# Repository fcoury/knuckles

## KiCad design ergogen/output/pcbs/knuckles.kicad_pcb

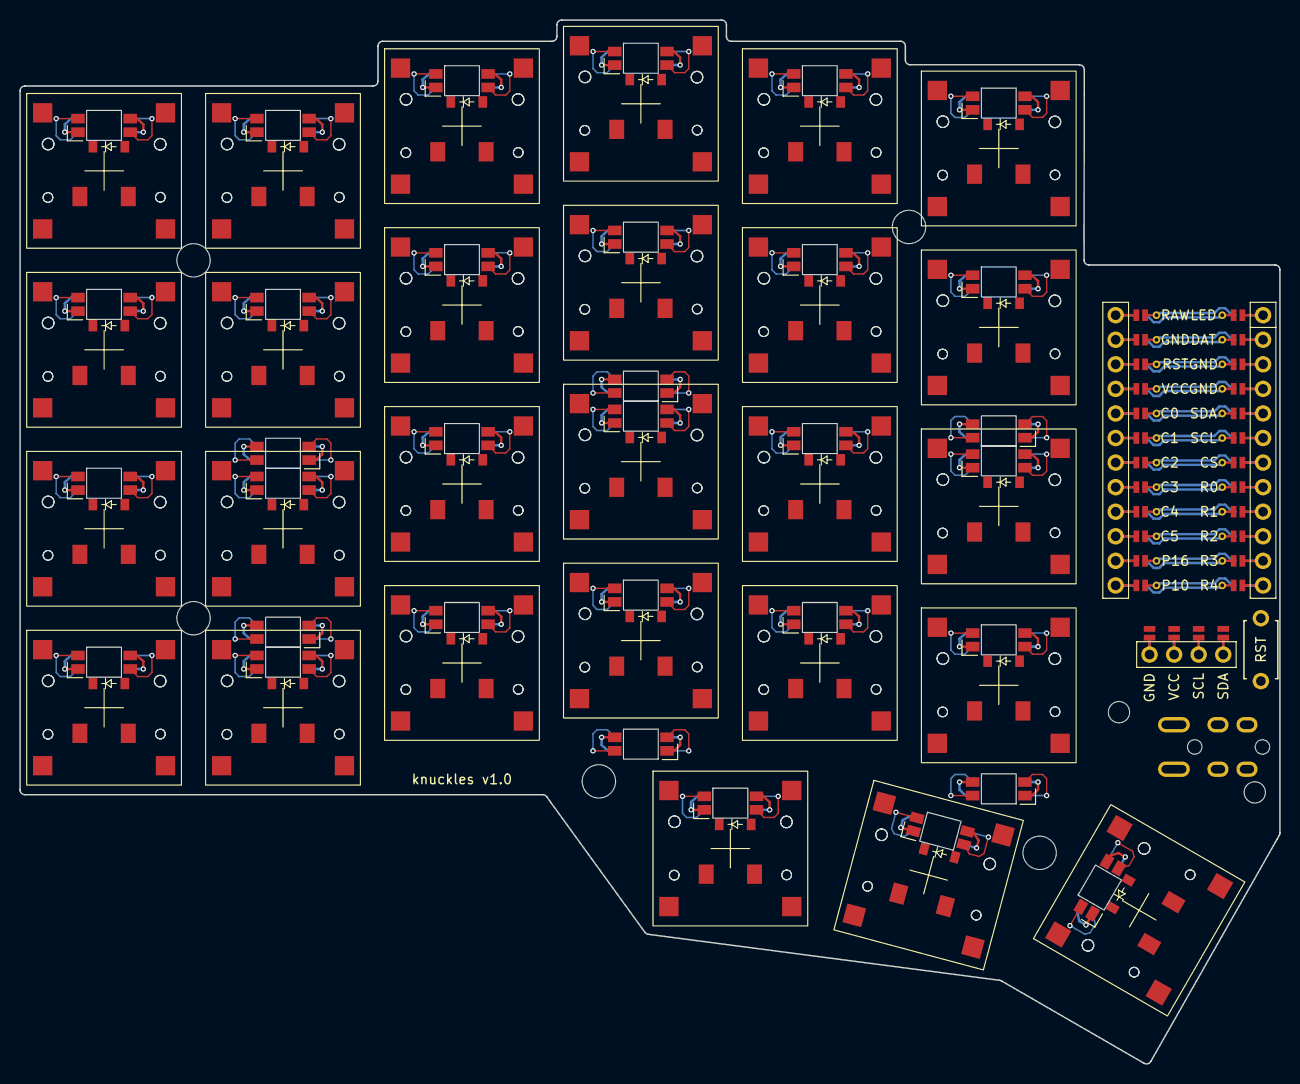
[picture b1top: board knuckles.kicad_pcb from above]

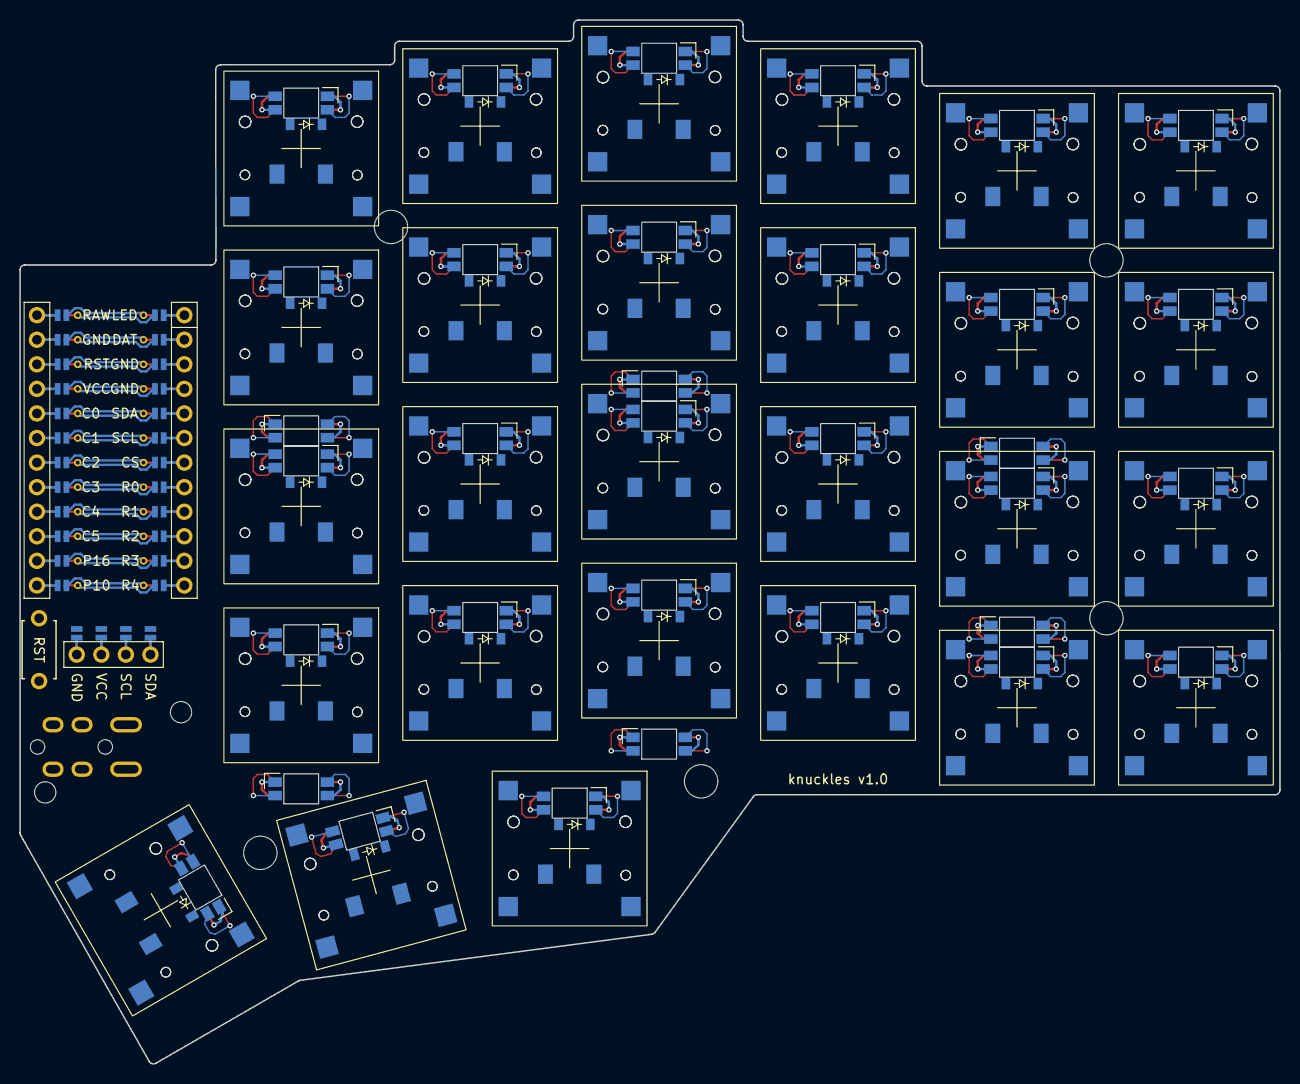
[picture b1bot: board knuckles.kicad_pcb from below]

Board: 2 copper layers, 130.3 x 107.9 mm, 152 parts (87 on the bottom side), 102 nets.

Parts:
D1, D2, D3, D4, D5, D6, D7, D8, D9, D10, D11, D12, D13, D14, D15, D16, D17, D18, D19, D20, D21, D22, D23, D24, D25, D26, D27, D28, D29, D30, D31, D32, D33, D34, D35, D36, D37, D38, D39, D40, D41, D42, D43, D44, D45, D46, D47, D48, D49, D50, D51, D52, D53, D54: diode_tht_sod123
DISP1: display_ssd1306
LED1, LED2, LED3, LED4, LED5, LED6, LED7, LED8, LED9, LED10, LED11, LED12, LED13, LED14, LED15, LED16, LED17, LED18, LED19, LED20, LED21, LED22, LED23, LED24, LED25, LED26, LED27: led_SK6812mini-e (per-key, reversible)
LED28, LED29, LED30, LED31, LED32, LED33: led_SK6812mini-e (underglow, reversible)
MCU1: mcu_nice_nano
MH1, MH2, MH3, MH4, MH5, MH6, MH7: mounting_hole_npth
RST1: reset_switch_tht_top
S1, S2, S3, S4, S5, S6, S7, S8, S9, S10, S11, S12, S13, S14, S15, S16, S17, S18, S19, S20, S21, S22, S23, S24, S25, S26, S27, S28, S29, S30, S31, S32, S33, S34, S35, S36, S37, S38, S39, S40, S41, S42, S43, S44, S45, S46, S47, S48, S49, S50, S51, S52, S53, S54: CPG1316S01D02
TRRS1: trrs_pj320a (reversible, symmetric)

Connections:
C0: MCU1.120, S1.1, S2.1, S3.1, S4.1, S28.1, S29.1, S30.1, S31.1
C1: MCU1.119, S5.1, S6.1, S7.1, S8.1, S32.1, S33.1, S34.1, S35.1
C2: MCU1.118, S9.1, S10.1, S11.1, S12.1, S36.1, S37.1, S38.1, S39.1
C3: MCU1.117, S13.1, S14.1, S15.1, S16.1, S25.1, S40.1, S41.1, S42.1, S43.1, S52.1
C4: MCU1.116, S17.1, S18.1, S19.1, S20.1, S26.1, S44.1, S45.1, S46.1, S47.1, S53.1
C5: MCU1.115, S21.1, S22.1, S23.1, S24.1, S27.1, S48.1, S49.1, S50.1, S51.1, S54.1
DAT: MCU1.102, TRRS1.3
DISP1_1: DISP1.1, DISP1.13, DISP1.20
DISP1_2: DISP1.2, DISP1.12, DISP1.21
DISP1_3: DISP1.3, DISP1.11, DISP1.22
DISP1_4: DISP1.4, DISP1.10, DISP1.23
GND: DISP1.14, DISP1.24, LED1.3, LED2.3, LED3.3, LED4.3, LED5.3, LED6.3, LED7.3, LED8.3, LED9.3, LED10.3, LED11.3, LED12.3, LED13.3, LED14.3, LED15.3, LED16.3, LED17.3, LED18.3, LED19.3, LED20.3, LED21.3, LED22.3, LED23.3, LED24.3, LED25.3, LED26.3, LED27.3, LED28.3, LED29.3, LED30.3, LED31.3, LED32.3, LED33.3, MCU1.103, MCU1.104, MCU1.123, RST1.2, TRRS1.2
LED: LED28.4, MCU1.101
LED_1: LED21.4, LED27.2
LED_2: LED21.2, LED22.4
LED_3: LED22.2, LED23.4
LED_4: LED19.4, LED23.2
LED_5: LED18.4, LED19.2
LED_6: LED17.4, LED18.2
LED_7: LED17.2, LED26.4
LED_8: LED25.4, LED26.2
LED_9: LED13.4, LED25.2
LED_10: LED13.2, LED14.4
LED_11: LED14.2, LED15.4
LED_12: LED11.4, LED15.2
LED_13: LED10.4, LED11.2
LED_14: LED9.4, LED10.2
LED_15: LED5.4, LED9.2
LED_16: LED5.2, LED6.4
LED_17: LED6.2, LED7.4
LED_18: LED3.4, LED7.2
LED_19: LED2.4, LED3.2
LED_20: LED1.4, LED2.2
R0: D4.1, D8.1, D12.1, D16.1, D20.1, D24.1, D31.1, D35.1, D39.1, D43.1, D47.1, D51.1, MCU1.108
R1: D3.1, D7.1, D11.1, D15.1, D19.1, D23.1, D30.1, D34.1, D38.1, D42.1, D46.1, D50.1, MCU1.109
R2: D2.1, D6.1, D10.1, D14.1, D18.1, D22.1, D29.1, D33.1, D37.1, D41.1, D45.1, D49.1, MCU1.110
R3: D1.1, D5.1, D9.1, D13.1, D17.1, D21.1, D28.1, D32.1, D36.1, D40.1, D44.1, D48.1, MCU1.111
R4: D25.1, D26.1, D27.1, D52.1, D53.1, D54.1, MCU1.112
RST: MCU1.122, RST1.1
SCL: DISP1.16, DISP1.26, MCU1.106
SDA: DISP1.17, DISP1.27, MCU1.105
ULED_1: LED28.2, LED29.4
ULED_2: LED29.2, LED30.4
ULED_3: LED30.2, LED31.4
ULED_4: LED31.2, LED32.4
ULED_5: LED32.2, LED33.4
ULED_6: LED27.4, LED33.2
VCC: DISP1.15, DISP1.25, LED1.1, LED2.1, LED3.1, LED4.1, LED5.1, LED6.1, LED7.1, LED8.1, LED9.1, LED10.1, LED11.1, LED12.1, LED13.1, LED14.1, LED15.1, LED16.1, LED17.1, LED18.1, LED19.1, LED20.1, LED21.1, LED22.1, LED23.1, LED24.1, LED25.1, LED26.1, LED27.1, LED28.1, LED29.1, LED30.1, LED31.1, LED32.1, LED33.1, MCU1.121, TRRS1.4
far_home_B: D27.2, S27.2
far_home_F: D54.2, S54.2
index_bottom_B: D17.2, S17.2
index_bottom_F: D44.2, S44.2
index_home_B: D18.2, S18.2
index_home_F: D45.2, S45.2
index_numbers_B: D20.2, S20.2
index_numbers_F: D47.2, S47.2
index_top_B: D19.2, S19.2
index_top_F: D46.2, S46.2
inner_bottom_B: D21.2, S21.2
inner_bottom_F: D48.2, S48.2
inner_home_B: D22.2, S22.2
inner_home_F: D49.2, S49.2
inner_numbers_B: D24.2, S24.2
inner_numbers_F: D51.2, S51.2
inner_top_B: D23.2, S23.2
inner_top_F: D50.2, S50.2
mid_home_B: D26.2, S26.2
mid_home_F: D53.2, S53.2
middle_bottom_B: D13.2, S13.2
middle_bottom_F: D40.2, S40.2
middle_home_B: D14.2, S14.2
middle_home_F: D41.2, S41.2
middle_numbers_B: D16.2, S16.2
middle_numbers_F: D43.2, S43.2
middle_top_B: D15.2, S15.2
middle_top_F: D42.2, S42.2
near_home_B: D25.2, S25.2
near_home_F: D52.2, S52.2
outer_bottom_B: D1.2, S1.2
outer_bottom_F: D28.2, S28.2
outer_home_B: D2.2, S2.2
outer_home_F: D29.2, S29.2
outer_numbers_B: D4.2, S4.2
outer_numbers_F: D31.2, S31.2
outer_top_B: D3.2, S3.2
outer_top_F: D30.2, S30.2
pinky_bottom_B: D5.2, S5.2
pinky_bottom_F: D32.2, S32.2
pinky_home_B: D6.2, S6.2
pinky_home_F: D33.2, S33.2
pinky_numbers_B: D8.2, S8.2
pinky_numbers_F: D35.2, S35.2
pinky_top_B: D7.2, S7.2
pinky_top_F: D34.2, S34.2
ring_bottom_B: D9.2, S9.2
ring_bottom_F: D36.2, S36.2
ring_home_B: D10.2, S10.2
ring_home_F: D37.2, S37.2
ring_numbers_B: D12.2, S12.2
ring_numbers_F: D39.2, S39.2
ring_top_B: D11.2, S11.2
ring_top_F: D38.2, S38.2
